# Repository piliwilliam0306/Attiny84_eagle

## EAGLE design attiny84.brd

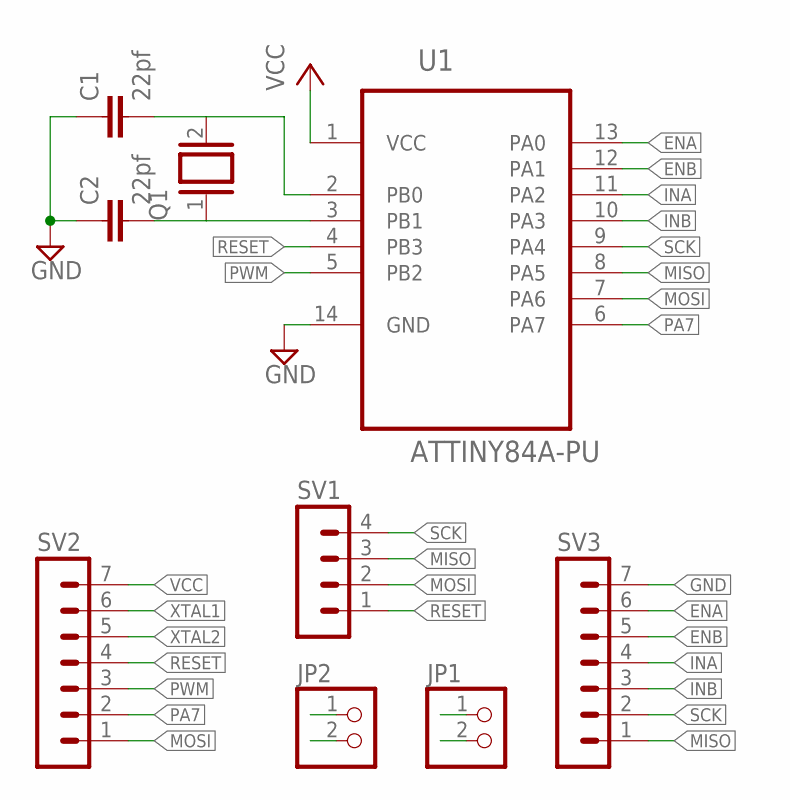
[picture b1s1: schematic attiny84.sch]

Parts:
C1, C2: 22pf; C2.5-2
JP1, JP2: PINHD-1X2; 1X02
Q1: XTAL/S; QS
SV1: MA04-1
SV2, SV3: MA07-1
U1: ATTINY84A-PU; DIP254P762X533-14

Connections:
ENA: SV3.6, U1.13 (PA0)
ENB: SV3.5, U1.12 (PA1)
GND: C1.1, C2.1, JP1.1, JP1.2, SV3.7, U1.14 (GND)
INA: SV3.4, U1.11 (PA2)
INB: SV3.3, U1.10 (PA3)
MISO: SV1.3, SV3.1, U1.8 (PA5)
MOSI: SV1.2, SV2.1, U1.7 (PA6)
PA7: SV2.2, U1.6 (PA7)
PWM: SV2.3, U1.5 (PB2)
RESET: SV1.1, SV2.4, U1.4 (PB3)
SCK: SV1.4, SV3.2, U1.9 (PA4)
VCC: JP2.1, JP2.2, SV2.7, U1.1 (VCC)
XTAL1: C1.2, Q1.2, SV2.6, U1.2 (PB0)
XTAL2: C2.2, Q1.1, SV2.5, U1.3 (PB1)

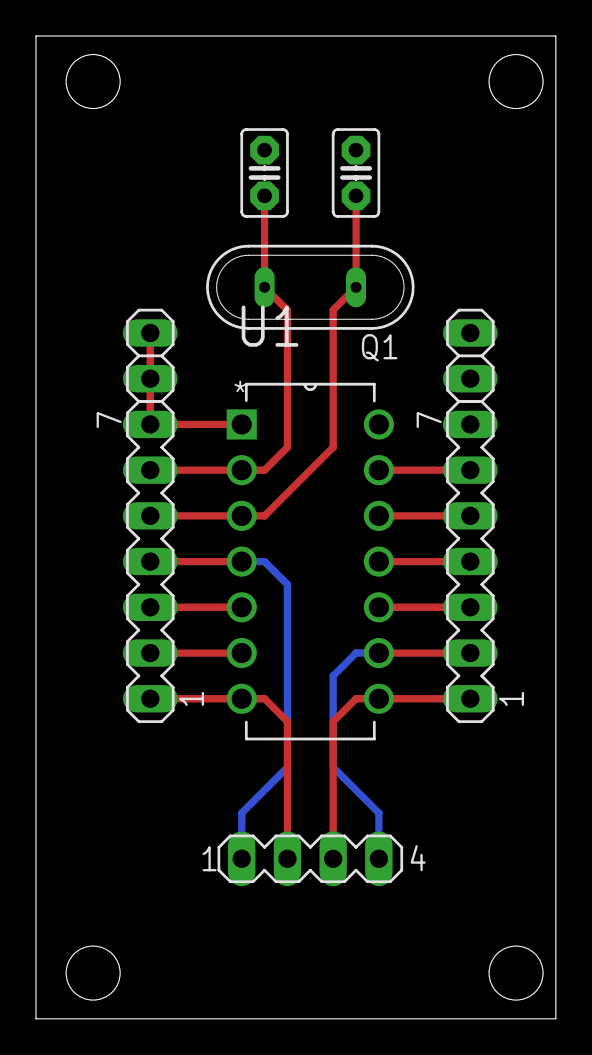
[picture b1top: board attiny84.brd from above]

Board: 2 copper layers, 28.9 x 54.6 mm, 9 parts (0 on the bottom side), 14 nets.

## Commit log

2015-12-17 add DI/DO
